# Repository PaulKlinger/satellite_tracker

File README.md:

This is the code and hardware design for my
[Satellite tracker](https://www.reddit.com/r/space/comments/9py5qd/i_made_a_thingy_that_shows_satellites_and_space/).

The orbit_np.py file is a modified version of [pyorbital](https://github.com/pytroll/pyorbital)
(it calculates the orbits of all the satellites at the same time to increase performance).

Requires https://github.com/PaulKlinger/LIBtft144 and https://github.com/jgarff/rpi_ws281x + a bunch of libraries from PyPi.

The PCB design for the LED boards is in the PCBs/LED folder. I've reversed the VCC/GND connections on one side of the pcb
compared to my version to make assembly easier. Files for three additional PCBs connecting the various parts are in the
PCB/auxiliary folder (these are not strictly necessary, I just used protoboard for the first version).

The STLs and Fusion 360 source for the 3d printed parts are in the "3D printed parts" folder.
Note that the 3d printer files are for a slightly earlier version of the auxiliary PCBs, which still had some issues.
So the current ones probably don't fit exactly, e.g. the display cutout might be slightly offset.

I'd strongly recommend that anyone who builds this uses threaded rods through the pillars instead of the million screws
I used. (I just didn't have any rods and wanted to build it right away.)

The 3 PCBs in the PCBs/auxiliary folder include:
* One which splits the incoming micro usb power between the RaspberryPi and the LED boards.
Contains a micro usb port, a 1000uf capacitor, a right angle micro usb coord to connect to the Pi, and a connector
(LED strip type) to connect power to the led boards.
* A header board which plugs into the Pi. Contains a 2*20 pin header, a SN74AHCT125N level shifter,
and a 4 pin and 10 pin "JST 1.25mm" connector (that's what they are called on aliexpress at least).
* And an interface board with a standard (6x6mm) push button, a 470 ohm resistor, a 3mm LED,
and the 1.44" tft (with ST7735 driver chip)

These 3 PCBs are combined onto one ~10*10cm panel. Many PCB manufacturers charge extra for panelized designs but
[dirtypcbs](https://dirtypcbs.com) doesn't.

The designs here fix some errors of the ones that I ordered. Assembled mine look like this:

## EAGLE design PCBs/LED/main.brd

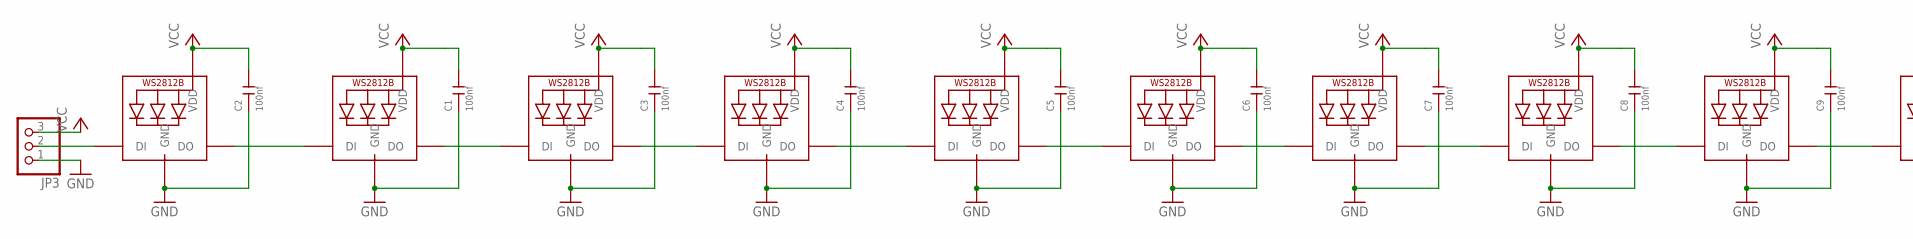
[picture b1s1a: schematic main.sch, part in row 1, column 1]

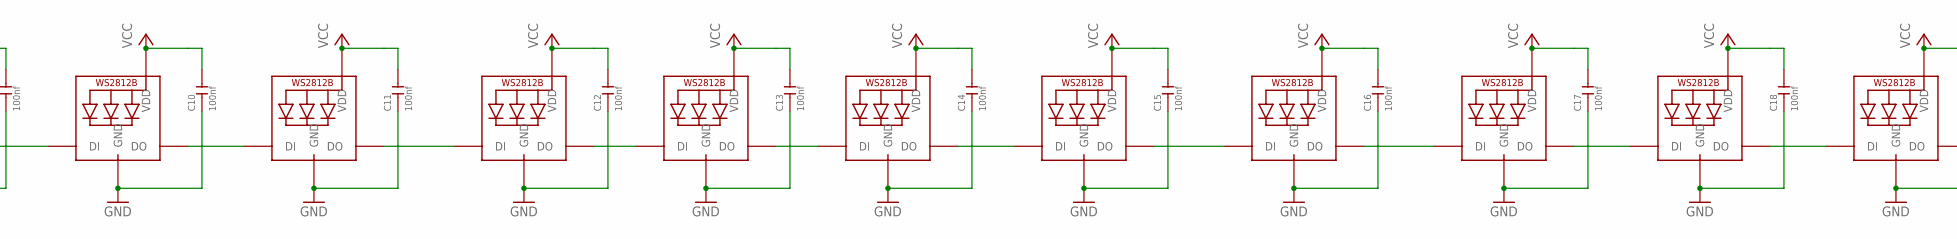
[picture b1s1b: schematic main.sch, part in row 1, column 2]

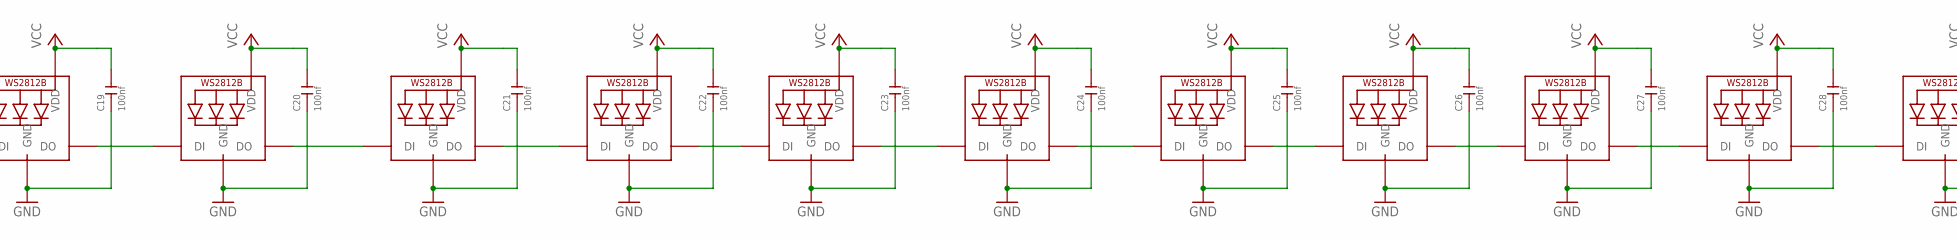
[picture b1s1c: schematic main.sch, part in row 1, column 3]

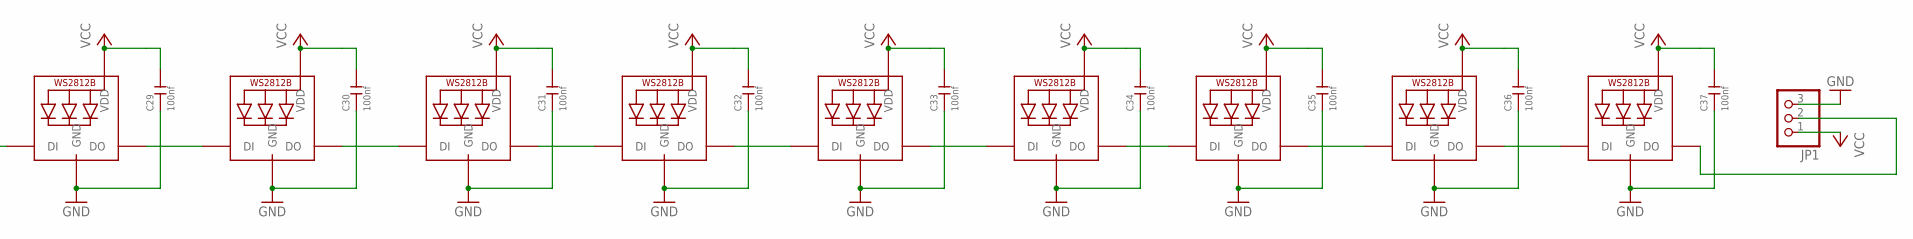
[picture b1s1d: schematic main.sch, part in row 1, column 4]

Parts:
C1, C2, C3, C4, C5, C6, C7, C8, C9, C10, C11, C12, C13, C14, C15, C16, C17, C18, C19, C20, C21, C22, C23, C24, C25, C26, C27, C28, C29, C30, C31, C32, C33, C34, C35, C36, C37: 100nf; C0805
JP1, JP3: PINHD-1X3; 1X03
L: WS2812B5050; WS2812B
LED1, LED3, LED4, LED5, LED6, LED7, LED8, LED9, LED10, LED11, LED12, LED13, LED14, LED15, LED16, LED17, LED18, LED19, LED20, LED21, LED22, LED23, LED24, LED25, LED26, LED27, LED28, LED29, LED30, LED31, LED32, LED33, LED34, LED35, LED36, LED37: WS2812B5050; WS2812B

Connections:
GND: C1.1, C2.1, C3.1, C4.1, C5.1, C6.1, C7.1, C8.1, C9.1, C10.1, C11.1, C12.1, C13.1, C14.1, C15.1, C16.1, C17.1, C18.1, C19.1, C20.1, C21.1, C22.1, C23.1, C24.1, C25.1, C26.1, C27.1, C28.1, C29.1, C30.1, C31.1, C32.1, C33.1, C34.1, C35.1, C36.1, C37.1, JP1.3, JP3.1, L.3-GND (GND), LED1.3-GND (GND), LED3.3-GND (GND), LED4.3-GND (GND), LED5.3-GND (GND), LED6.3-GND (GND), LED7.3-GND (GND), LED8.3-GND (GND), LED9.3-GND (GND), LED10.3-GND (GND), LED11.3-GND (GND), LED12.3-GND (GND), LED13.3-GND (GND), LED14.3-GND (GND), LED15.3-GND (GND), LED16.3-GND (GND), LED17.3-GND (GND), LED18.3-GND (GND), LED19.3-GND (GND), LED20.3-GND (GND), LED21.3-GND (GND), LED22.3-GND (GND), LED23.3-GND (GND), LED24.3-GND (GND), LED25.3-GND (GND), LED26.3-GND (GND), LED27.3-GND (GND), LED28.3-GND (GND), LED29.3-GND (GND), LED30.3-GND (GND), LED31.3-GND (GND), LED32.3-GND (GND), LED33.3-GND (GND), LED34.3-GND (GND), LED35.3-GND (GND), LED36.3-GND (GND), LED37.3-GND (GND)
unnamed: L.2-DOUT (DO), LED1.4-DIN (DI)
unnamed: LED1.2-DOUT (DO), LED3.4-DIN (DI)
unnamed: LED3.2-DOUT (DO), LED4.4-DIN (DI)
unnamed: LED4.2-DOUT (DO), LED5.4-DIN (DI)
unnamed: LED5.2-DOUT (DO), LED6.4-DIN (DI)
unnamed: LED6.2-DOUT (DO), LED7.4-DIN (DI)
unnamed: LED7.2-DOUT (DO), LED8.4-DIN (DI)
unnamed: LED8.2-DOUT (DO), LED9.4-DIN (DI)
unnamed: LED9.2-DOUT (DO), LED10.4-DIN (DI)
unnamed: LED10.2-DOUT (DO), LED11.4-DIN (DI)
unnamed: LED11.2-DOUT (DO), LED12.4-DIN (DI)
unnamed: LED12.2-DOUT (DO), LED13.4-DIN (DI)
unnamed: LED13.2-DOUT (DO), LED14.4-DIN (DI)
unnamed: LED14.2-DOUT (DO), LED15.4-DIN (DI)
unnamed: LED15.2-DOUT (DO), LED16.4-DIN (DI)
unnamed: LED16.2-DOUT (DO), LED17.4-DIN (DI)
unnamed: LED17.2-DOUT (DO), LED18.4-DIN (DI)
unnamed: LED18.2-DOUT (DO), LED19.4-DIN (DI)
unnamed: LED19.2-DOUT (DO), LED20.4-DIN (DI)
unnamed: LED20.2-DOUT (DO), LED21.4-DIN (DI)
unnamed: LED21.2-DOUT (DO), LED22.4-DIN (DI)
unnamed: LED22.2-DOUT (DO), LED23.4-DIN (DI)
unnamed: LED23.2-DOUT (DO), LED24.4-DIN (DI)
unnamed: LED24.2-DOUT (DO), LED25.4-DIN (DI)
unnamed: LED25.2-DOUT (DO), LED26.4-DIN (DI)
unnamed: LED26.2-DOUT (DO), LED27.4-DIN (DI)
unnamed: LED27.2-DOUT (DO), LED28.4-DIN (DI)
unnamed: LED28.2-DOUT (DO), LED29.4-DIN (DI)
unnamed: LED29.2-DOUT (DO), LED30.4-DIN (DI)
unnamed: LED30.2-DOUT (DO), LED31.4-DIN (DI)
unnamed: LED31.2-DOUT (DO), LED32.4-DIN (DI)
unnamed: LED32.2-DOUT (DO), LED33.4-DIN (DI)
unnamed: LED33.2-DOUT (DO), LED34.4-DIN (DI)
unnamed: LED34.2-DOUT (DO), LED35.4-DIN (DI)
unnamed: LED35.2-DOUT (DO), LED36.4-DIN (DI)
unnamed: LED36.2-DOUT (DO), LED37.4-DIN (DI)
unnamed: JP3.2, L.4-DIN (DI)
unnamed: JP1.2, LED37.2-DOUT (DO)
VCC: C1.2, C2.2, C3.2, C4.2, C5.2, C6.2, C7.2, C8.2, C9.2, C10.2, C11.2, C12.2, C13.2, C14.2, C15.2, C16.2, C17.2, C18.2, C19.2, C20.2, C21.2, C22.2, C23.2, C24.2, C25.2, C26.2, C27.2, C28.2, C29.2, C30.2, C31.2, C32.2, C33.2, C34.2, C35.2, C36.2, C37.2, JP1.1, JP3.3, L.1-VDD (VDD), LED1.1-VDD (VDD), LED3.1-VDD (VDD), LED4.1-VDD (VDD), LED5.1-VDD (VDD), LED6.1-VDD (VDD), LED7.1-VDD (VDD), LED8.1-VDD (VDD), LED9.1-VDD (VDD), LED10.1-VDD (VDD), LED11.1-VDD (VDD), LED12.1-VDD (VDD), LED13.1-VDD (VDD), LED14.1-VDD (VDD), LED15.1-VDD (VDD), LED16.1-VDD (VDD), LED17.1-VDD (VDD), LED18.1-VDD (VDD), LED19.1-VDD (VDD), LED20.1-VDD (VDD), LED21.1-VDD (VDD), LED22.1-VDD (VDD), LED23.1-VDD (VDD), LED24.1-VDD (VDD), LED25.1-VDD (VDD), LED26.1-VDD (VDD), LED27.1-VDD (VDD), LED28.1-VDD (VDD), LED29.1-VDD (VDD), LED30.1-VDD (VDD), LED31.1-VDD (VDD), LED32.1-VDD (VDD), LED33.1-VDD (VDD), LED34.1-VDD (VDD), LED35.1-VDD (VDD), LED36.1-VDD (VDD), LED37.1-VDD (VDD)

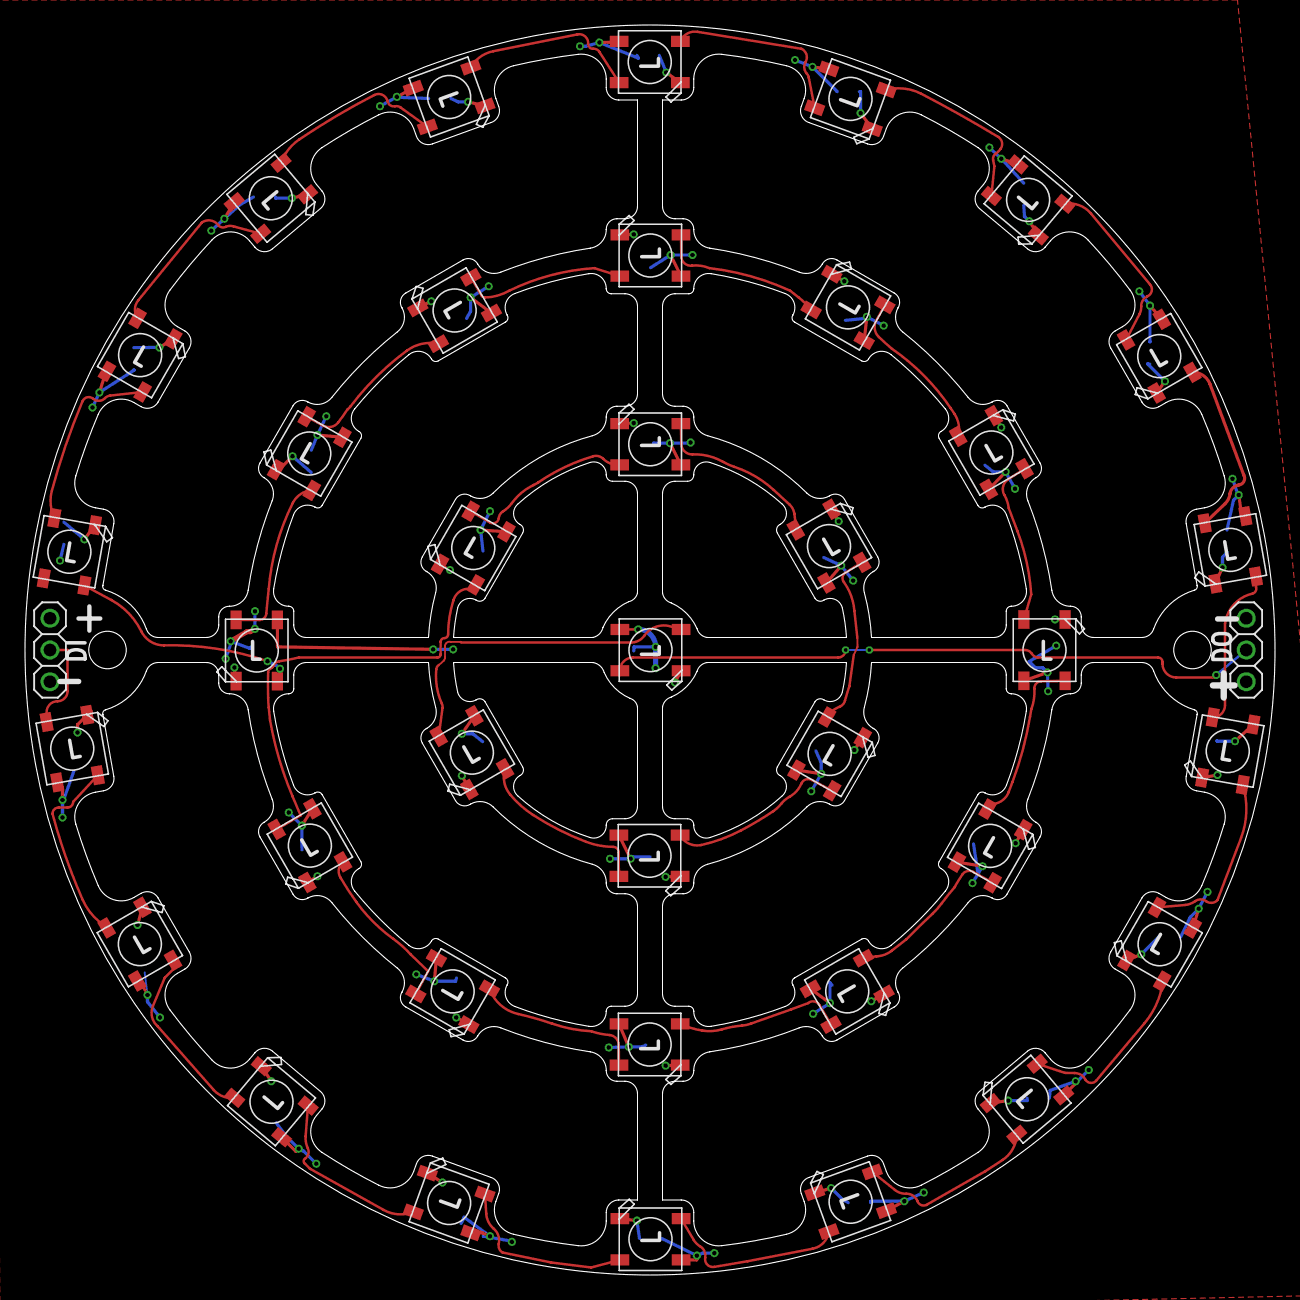
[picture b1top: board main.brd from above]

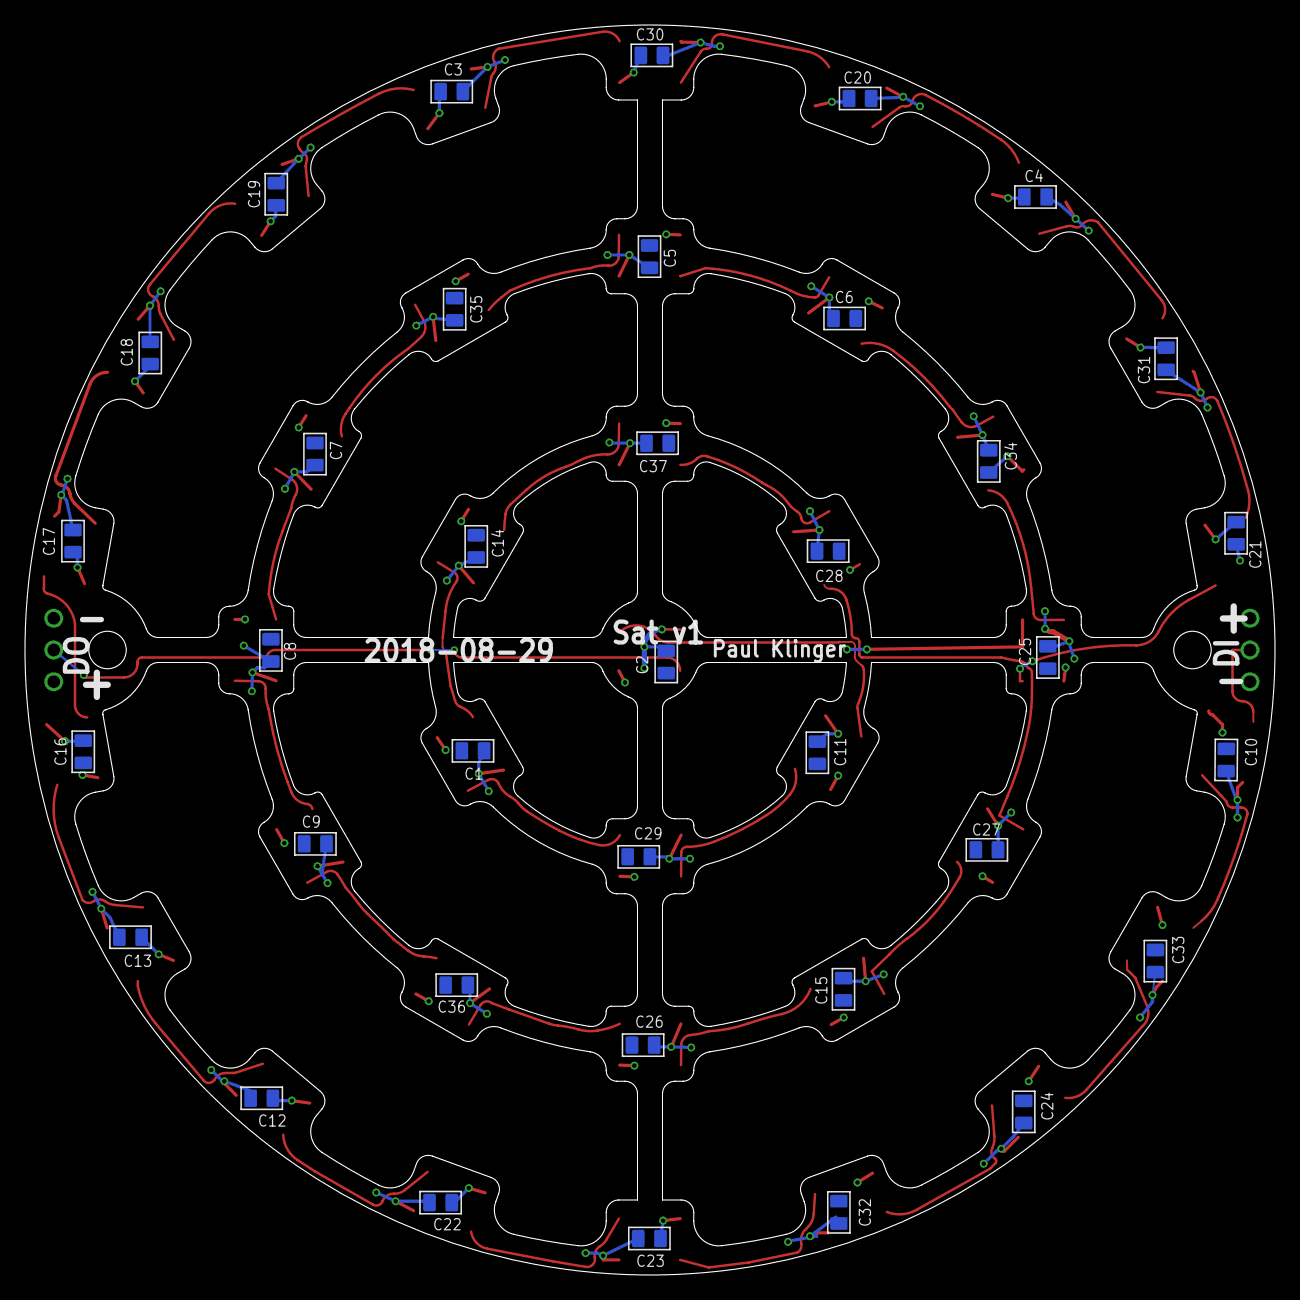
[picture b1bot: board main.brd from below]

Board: 2 copper layers, 100.0 x 100.0 mm, 76 parts (37 on the bottom side), 40 nets.

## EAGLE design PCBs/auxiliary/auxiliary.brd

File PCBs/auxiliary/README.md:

The files in this directory include 3 PCBs:
* One which splits the incoming micro usb power between the RaspberryPi and the LED boards.
Contains a micro usb port, a 1000uf capacitor, a right angle micro usb coord to connect to the Pi, and a connector
(LED strip type) to connect power to the led boards.
* A header board which plugs into the Pi. Contains a 2*20 pin header, a SN74AHCT125N level shifter,
and a 4 pin and 10 pin "JST 1.25mm" connector (that's what they are called on aliexpress at least).
* And a interface board with a standard (6x6mm) push button, a 470 ohm resistor, a 3mm LED,
and the 1.44" tft (with ST7735 driver chip)

The 3 PCBs are combined onto one ~10*10cm panel. Many PCB manufacturers charge extra for panelized designs but
[dirtypcbs](https://dirtypcbs.com) doesn't.

The designs here fix some errors of the ones that I ordered. Assembled mine look like this:

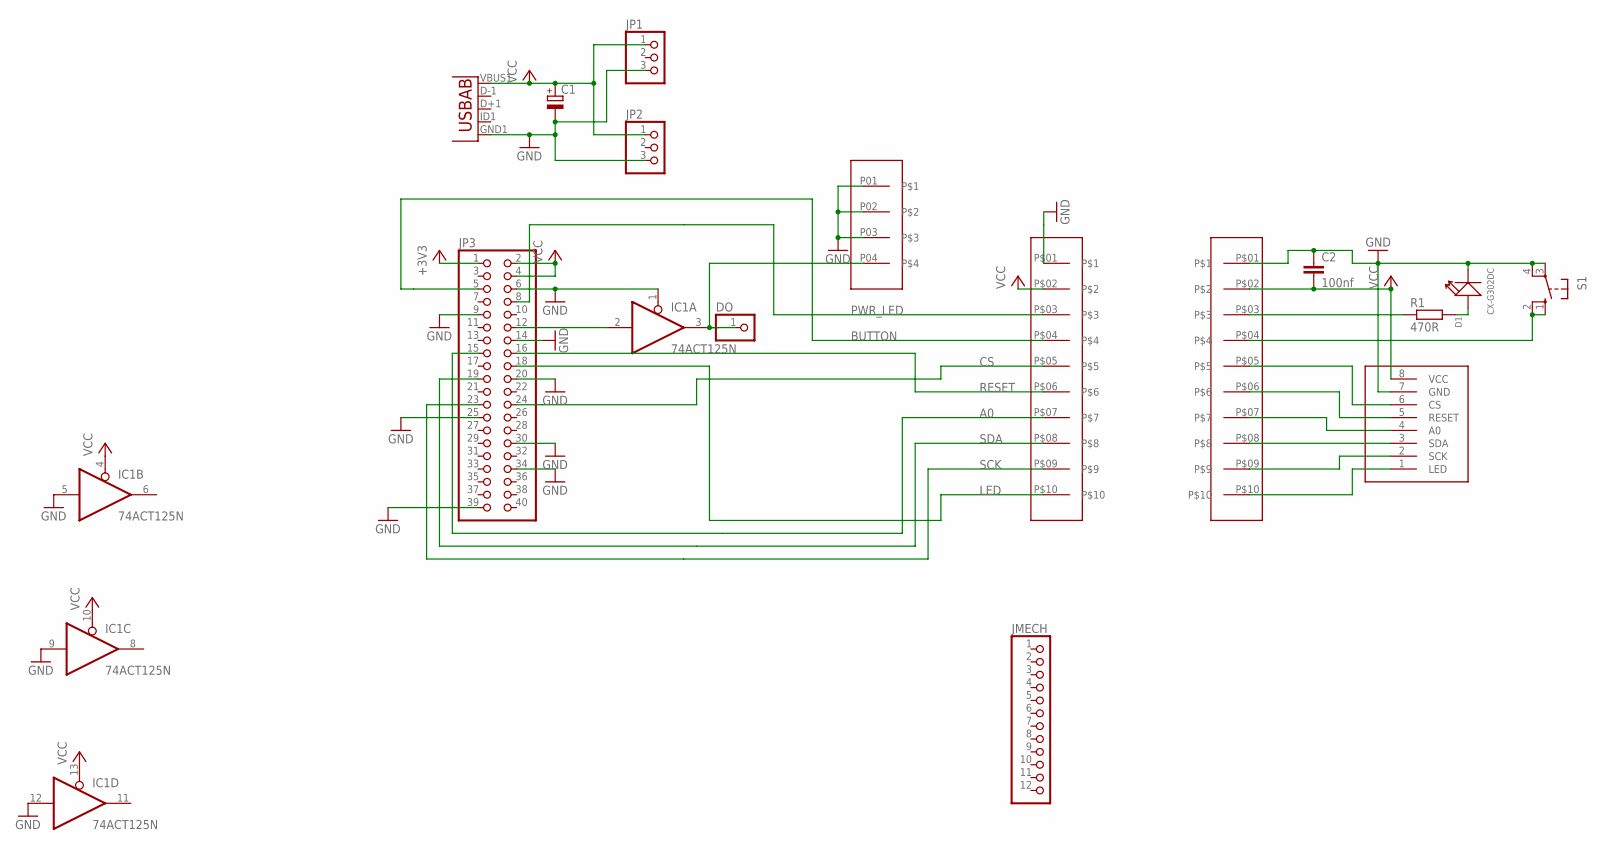
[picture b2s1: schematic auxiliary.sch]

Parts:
C1: CPOL-EUE5-10.5; E5-10,5
C2: 100nf; C025-030X050
D1: CX-G302DC; LED2-2.54-D3.0MM
DO: PINHD-1X1; 1X01
IC1: 74ACT125N; DIL14
J1, J2: JST1.25_10PIN
JMECH: PINHD-1X12; 1X12
JP1, JP2: PINHD-1X3; 1X03
JP3: PINHD-2X20; 2X20
R1: 470R; 0207/7
S1: 10-XX; B3F-10XX
U1: USB-THROUGH; USB-MICRO-THROUGH
U$2: SPI_TFT_1.44"
U$3: JST1.25_4PIN

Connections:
+3V3: JP3.1
A0: J1.P$07, JP3.15
BUTTON: J1.P$04, JP3.5
CS: J1.P$05, JP3.24
GND: C1.-, C2.1, D1.K (-), IC1.1 (OE), IC1.5 (I), IC1.7 (GND), IC1.9 (I), IC1.12 (I), J1.P$01, J2.P$01, JP1.3, JP2.3, JP3.6, JP3.9, JP3.14, JP3.20, JP3.25, JP3.30, JP3.34, JP3.39, S1.3, S1.4 (P1), U1.GND1 (GND), U$2.7 (GND), U$3.P01, U$3.P02, U$3.P03
LED: J1.P$10, JP3.18
unnamed: D1.A (+), R1.2
unnamed: DO.1, IC1.3 (O), U$3.P04
unnamed: IC1.2 (I), JP3.12
unnamed: J2.P$05, U$2.6 (CS)
unnamed: J2.P$06, U$2.5 (RESET)
unnamed: J2.P$07, U$2.4 (A0)
unnamed: J2.P$08, U$2.3 (SDA)
unnamed: J2.P$09, U$2.2 (SCK)
unnamed: J2.P$03, R1.1
unnamed: J2.P$10, U$2.1 (LED)
unnamed: J2.P$04, S1.1 (S), S1.2 (S1)
PWR_LED: J1.P$03, JP3.8
RESET: J1.P$06, JP3.16
SCK: J1.P$09, JP3.23
SDA: J1.P$08, JP3.19
VCC: C1.+, C2.2, IC1.4 (OE), IC1.10 (OE), IC1.13 (OE), IC1.14 (VCC), J1.P$02, J2.P$02, JP1.1, JP2.1, JP3.2, JP3.4, U1.VBUS1 (VBUS), U$2.8 (VCC)

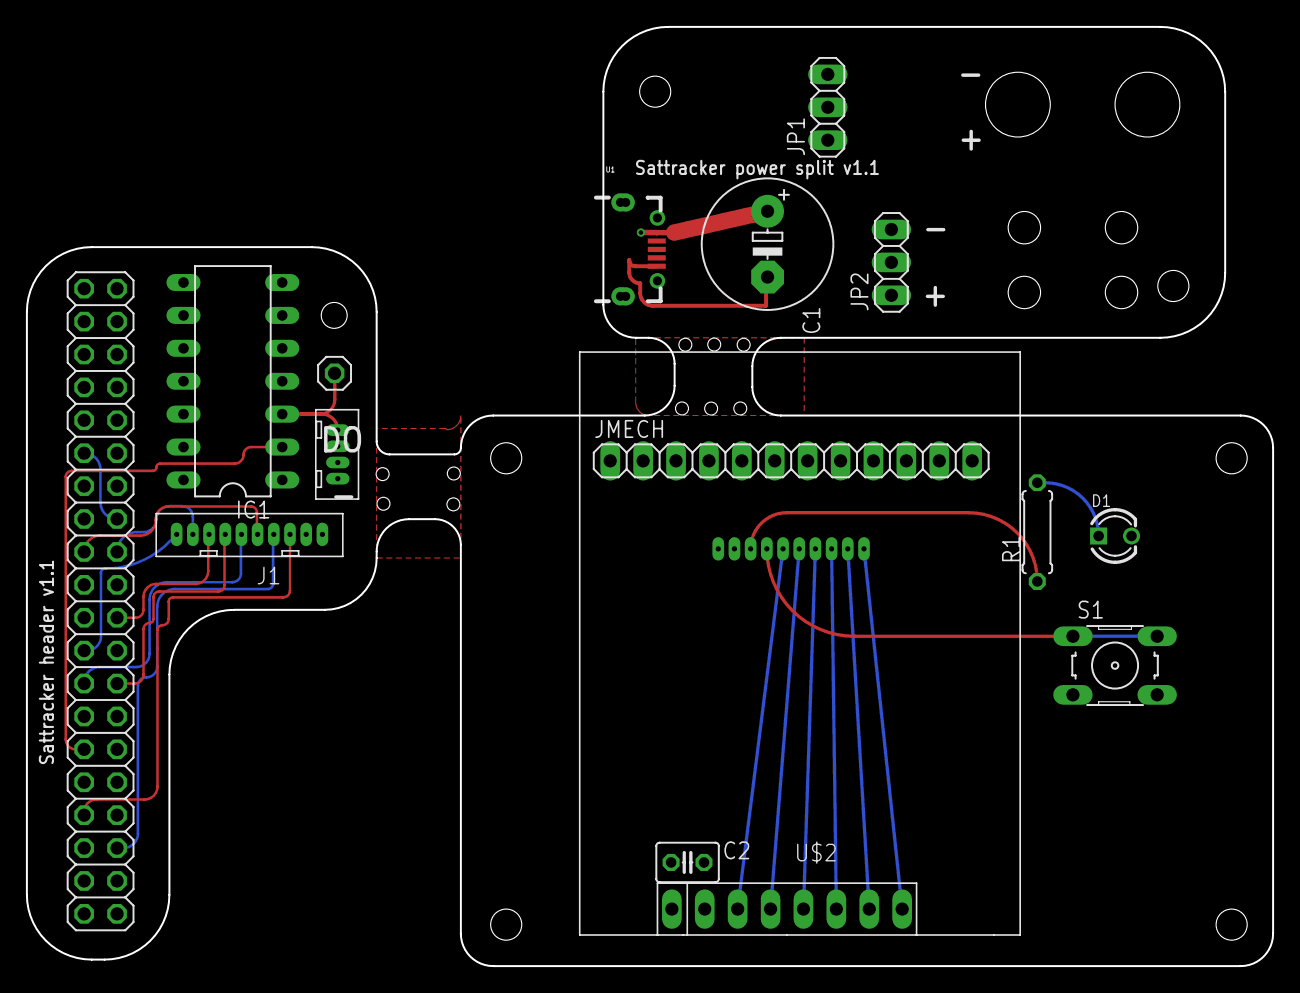
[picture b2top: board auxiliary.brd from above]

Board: 2 copper layers, 96.2 x 72.5 mm, 16 parts (1 on the bottom side), 21 nets.

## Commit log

2018-09-30 performance improvement??
    didn't really make much difference
2018-09-30 limit update rate
2018-09-30 added "rings" animation to demo mode
2018-09-30 optimized distance culling
2018-09-30 added priorities for overlapping sats
2018-09-30 added green color for highly interesting sats
2018-09-30 created planetlabs class
2018-09-30 fixed loop when updating tle
2018-09-30 improved handling of colors/priorities
2018-09-30 added spinning demo mode
2018-09-30 removed obsolete code
2018-10-01 added startup animation (new alternate animation)
    maybe change to something different later?
2018-10-01 don't recalculate led step size when getting same config again
    this would cause the step size to be halved if the next update came in before the switch was complete
2018-10-01 made it possible to stay in demo mode forever
    Making pretty colors wasn't really the point of this project...
2018-10-02 fixed direction of spinning animation, reverted loading message
2018-10-10 fix displaying satellite names after showing message
2018-10-20 added some comments to orbit_np.py
2018-10-20 removed LIBtft144 from repo (in separate repo now)
2018-10-20 added readme file
2018-10-20 moved spacetrack credentials out of repository
2018-10-20 added license
2018-10-20 added stl files for 3d printed part and LED PCB files
2018-10-20 added BOM
2018-10-20 added comment
2018-10-21 added fusion 360 source file
2018-10-21 added link to project video
2018-10-22 some code cleanup
2018-10-22 readme
2018-10-22 some more cleanup
2018-10-22 tweaked led arrangement to fit better with actual pcb
2018-10-22 check if the TLE file is actually over
2018-10-23 cleanup
2018-10-23 reorganized code (got rid of nonlocal variables and nested function)
2018-10-23 added some more type hints and convenience functions
2018-10-23 moved constants to separate file
2018-10-25 some more types, corrected number of text lines on display
2018-10-25 some more types
2018-10-25 added basic retry logic to tle download
2018-10-25 reversed VCC/GND connections of LED PCB to simplify assembly
2018-10-25 corrected silkscreen label for LED PCB connections
2018-11-03 added auxiliary PCBs
2018-11-03 updated 3d printed part for new aux PCBs
    Note that these are for a slightly earlier version of the PCBs so e.g. the display cutout might not fit exactly.
2018-11-03 updated to new display type
2018-11-03 adjusted cutout for usb power cord
2018-11-04 added picture and explanations of aux PCBs
2018-11-04 added comment about button functions
2018-11-04 sort satellites on display by priority
2018-11-12 uncompressed gerbers
2018-11-12 combined readme files
2018-11-12 ignore gerber files for github language detection
2019-01-21 updated video link image
2020-04-13 changed size of capacitors from 0401 to 0805
    (schematic not updated yet...)
2020-04-13 updated bom and schematic
2020-04-17 moved component designators to avoid overlaps
